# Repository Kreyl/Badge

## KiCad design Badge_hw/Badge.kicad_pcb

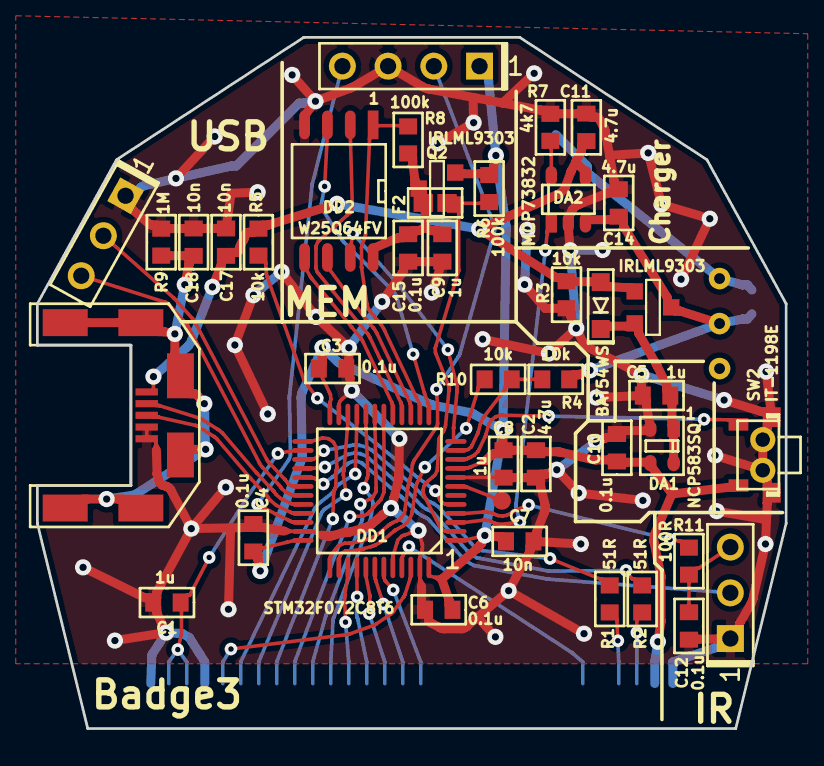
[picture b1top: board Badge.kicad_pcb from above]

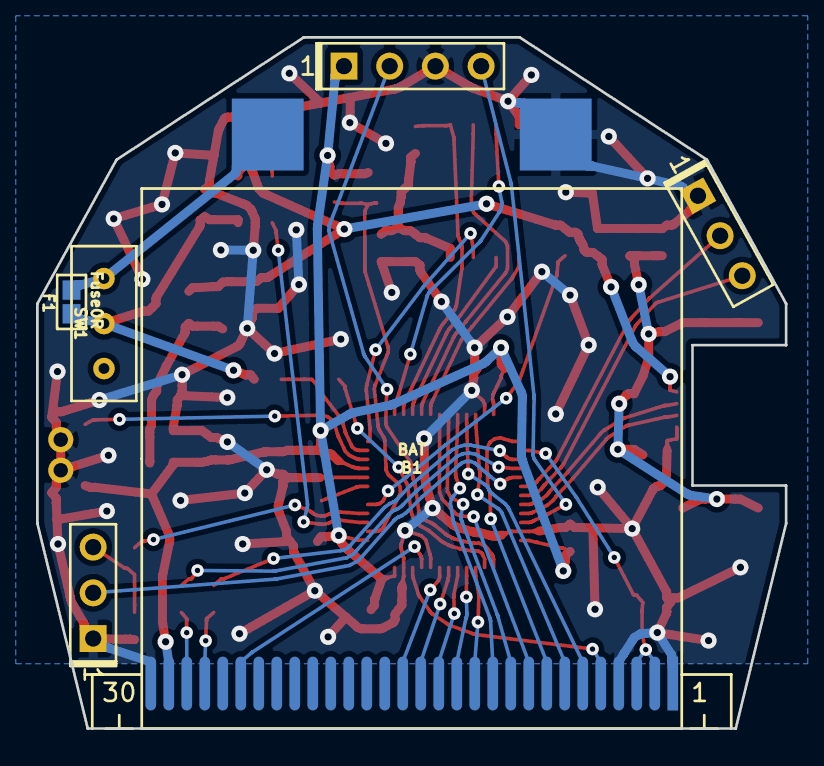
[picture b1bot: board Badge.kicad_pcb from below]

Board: 2 copper layers, 41.6 x 38.4 mm, 45 parts (5 on the bottom side), 49 nets.

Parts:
B1: BAT; EEMB603030
C1, C5, C8, C9: 1u; CAP_0603
C2, C11, C14: 4.7u; CAP_0603
C3, C4, C6, C10, C12, C15: 0.1u; CAP_0603
C7, C17, C18: 10n; CAP_0603
D1: BAT54WS; SOD323
DA1: NCP583SQ; SC82AB
DA2: MCP73832; SOT23-5
DD1: STM32F072C8T6; LQFP48
DD2: W25Q64FV; SO8_208MIL
F1, F2: Fuse0R; RES_0603_FUSE
Q1, Q2: IRLML9303; SOT23-3
R1, R2: 51R; RES_0603
R3, R4, R5, R10: 10k; RES_0603
R6, R8: 100k; RES_0603
R7: 4k7; RES_0603
R9: 1M; RES_0603
R11: 100R; RES_0603
SW1: SWITCH; SW_SS-1P2T
SW2: IT-1198E; BTN_IT1198
TP1: TESTPOINT; TESTPOINT_1MM
U1: Round2.2; Round2_2
XL1: ST_SWD; PLS-4
XL2: USB_MINI_B; USBmicro_MOLEX_WM17142
XL3, XL4: CONN_3; PLS-3

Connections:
+3.3V: C2.1, C3.1, C4.1, C6.1, C7.1, C8.1, C10.1, DA1.3, DD1.1, DD1.9, DD1.24, DD1.36, DD1.48, Q2.2, R6.1, SW2.1, U1.29, XL1.1
+5V: C11.1, C17.2, D1.A, DA2.4, Q1.1, R3.1, R5.1, XL2.1
+BATT: C14.1, DA2.3, F1.1, Q1.3, R4.1, SW1.2
/BAT: B1.A, F1.2, SW1.1
/BatMeas: DD1.11, R4.2, R10.1
/Btn: DD1.10, SW2.2
/Charge: DA2.1, DD1.3
/D00: DD1.18, U1.9
/D01: DD1.19, U1.10
/D02: DD1.20, U1.11
/D03: DD1.39, U1.12
/D04: DD1.40, U1.13
/D05: DD1.41, U1.14
/D06: DD1.42, U1.15
/D07: DD1.43, U1.16
/D+: DD1.33, XL2.3
/D-: DD1.32, XL2.2
/IR_PWR: DD1.4, R11.2
/IR_RX: DD1.29, XL4.2
/LCD_CS: DD1.46, U1.5
/LCD_PWR: C1.1, DD1.26, U1.2, U1.3
/LCD_RD: DD1.25, U1.8
/LCD_RS: DD1.21, U1.6
/LCD_RST: DD1.45, U1.25
/LCD_WR: DD1.22, U1.7
/LED_C1: DD1.27, R1.1
/LED_C2: DD1.28, R2.1
/MEM_CLK: DD1.15, DD2.6
/MEM_CS: DD1.14, DD2.1, R8.2
/MEM_DI: DD1.17, DD2.5
/MEM_DO: DD1.16, DD2.2
/MEM_HOLD: DD1.12, DD2.7
/MEM_PWR: C9.1, C15.1, DD2.8, F2.2, Q2.3, R8.1
/MEM_PWR_CTRL: DD1.2, F2.1, Q2.1, R6.2
/MEM_WP: DD1.13, DD2.3
/RX: DD1.31, XL3.3
/SHLD: C18.1, R9.1, XL2.SHLD
/SWCLK: DD1.37, XL1.2
/SWDIO: DD1.34, XL1.4
/TX: DD1.30, XL3.2
/V_OUT: C5.1, D1.C, DA1.1, DA1.4, Q1.2
GND: B1.C, C1.2, C2.2, C3.2, C4.2, C5.2, C6.2, C7.2, C8.2, C9.2, C10.2, C11.2, C12.1, C14.2, C15.2, C17.1, C18.2, DA1.2, DA2.2, DD1.8, DD1.23, DD1.35, DD1.44, DD1.47, DD2.4, R3.2, R7.2, R9.2, SW2.H, U1.1, U1.4, U1.30, XL1.3, XL2.4, XL2.5, XL3.1, XL4.1
unnamed: C12.2, R11.1, XL4.3
unnamed: DA2.5, R7.1
unnamed: DD1.5, R5.2
unnamed: DD1.7, TP1.1
unnamed: DD1.38, R10.2
unnamed: R1.2, U1.27
unnamed: R2.2, U1.28

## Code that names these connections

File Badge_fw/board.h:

/*
 * board.h
 *
 *  Created on: 12 ñåíò. 2015 ã.
 *      Author: Kreyl
 */

#pragma once

#include <inttypes.h>

// ==== General ====
#define BOARD_NAME          "Badge3"
// MCU type as defined in the ST header.
#define STM32F072xB

// Freq of external crystal if any. Leave it here even if not used.
#define CRYSTAL_FREQ_HZ     12000000

#define SYS_TIM_CLK         (Clk.APBFreqHz * Clk.TimerClkMulti)

#if 1 // ========================== GPIO =======================================
// UART
#define UART_GPIO       GPIOA
#define UART_TX_PIN     9
#define UART_RX_PIN     10
#define UART_AF         AF1

// USB
#define USB_GPIO		GPIOA
#define USB_DM_PIN		11
#define USB_DP_PIN		12
#define SNS_5V_GPIO     GPIOF
#define SNS_5V_PIN      0

// Button
#define BTN_GPIO        GPIOA
#define BTN_PIN         0

// Battery Management
#define BAT_MEAS_GPIO   GPIOA
#define BAT_MEAS_PIN    1
#define BAT_SW_GPIO     GPIOA
#define BAT_SW_PIN      15
#define BAT_CHARGE_GPIO GPIOC
#define BAT_CHARGE_PIN  14

#if 1 // ==== LCD ====
#define LCD_GPIO        GPIOB
#define LCD_RST         8
#define LCD_CS          9
#define LCD_RS          10
#define LCD_WR          11
#define LCD_RD          12
#define LCD_PWR         13
#define LCD_MODE_MSK_READ   0xFFFF0000
#define LCD_MODE_MSK_WRITE  0x00005555
#define LCD_BCKLT_GPIO  GPIOB
#define LCD_BCKLT_PIN1  14
#define LCD_BCKLT_PIN2  15
#endif // LCD

#if 1 // ==== Flash W25Q64 ====
#define MEM_GPIO        GPIOA
#define MEM_CS          4
#define MEM_CLK         5
#define MEM_DI          7
#define MEM_DO          6
#define MEM_WP          3
#define MEM_HOLD        2
#define MEM_PWR_GPIO    GPIOC
#define MEM_PWR         13
#define MEM_SPI_AF      AF0
#endif // Flash

#endif // GPIO

#if 1 // ========================= Timer =======================================
// LCD
#define LCD_BCKLT_TMR   TIM15
#define LCD_BCKLT_CHNL1 1
#define LCD_BCKLT_CHNL2 2
#endif // Timer

#if 1 // =========================== SPI =======================================
#define MEM_SPI         SPI1
#endif

#if 1 // ========================== USART ======================================
#define UART            USART1
#define UART_TX_REG     UART->TDR
#define UART_RX_REG     UART->RDR
#endif

#if 1 // ========================= Inner ADC ===================================
#define ADC_REQUIRED        TRUE
// Clock divider: clock is generated from the APB2
#define ADC_CLK_DIVIDER		adcDiv2

// ADC channels
#define BAT_CHNL 	        1

#define ADC_VREFINT_CHNL    17  // All 4xx and F072 devices. Do not change.
#define ADC_CHANNELS        { BAT_CHNL, ADC_VREFINT_CHNL }
#define ADC_CHANNEL_CNT     2   // Do not use countof(AdcChannels) as preprocessor does not know what is countof => cannot check
#define ADC_SAMPLE_TIME     ast55d5Cycles
#define ADC_SAMPLE_CNT      8   // How many times to measure every channel

#define ADC_MAX_SEQ_LEN     16  // 1...16; Const, see ref man
#define ADC_SEQ_LEN         (ADC_SAMPLE_CNT * ADC_CHANNEL_CNT)
#if (ADC_SEQ_LEN > ADC_MAX_SEQ_LEN) || (ADC_SEQ_LEN == 0)
#error "Wrong ADC channel count and sample count"
#endif
#endif

#if 1 // ========================== USB ========================================
#define USBDrv          USBD1   // USB driver to use

// CRS
#define CRS_PRESCALER   RCC_CRS_SYNC_DIV1
#define CRS_SOURCE      RCC_CRS_SYNC_SOURCE_USB
#define CRS_POLARITY    RCC_CRS_SYNC_POLARITY_RISING
#define CRS_RELOAD_VAL  ((48000000 / 1000) - 1) // Ftarget / Fsync - 1
#define CRS_ERROR_LIMIT 34
#define HSI48_CALIBRATN 32
#endif // USB

#if 1 // =========================== DMA =======================================
#define STM32_DMA_REQUIRED  TRUE
// ==== Uart ====
// Remap is made automatically if required
#define UART_DMA_TX     STM32_DMA1_STREAM4
#define UART_DMA_RX     STM32_DMA1_STREAM5
#define UART_DMA_CHNL   0   // Dummy

// ==== Memory ====
#define SPI1_DMA_RX     STM32_DMA1_STREAM2

#define MEMCPY_DMA      STM32_DMA1_STREAM3
#define MEM_CPY_DMA_MODE STM32_DMA_CR_CHSEL(0) |    /* dummy */ \
                        STM32_DMA_CR_PL(0b10) |     /* DMA_PRIORITY_HIGH */ \
                        STM32_DMA_CR_MSIZE_BYTE | \
                        STM32_DMA_CR_PSIZE_BYTE

#if ADC_REQUIRED
/* DMA request mapped on this DMA channel only if the corresponding remapping bit is cleared in the SYSCFG_CFGR1
 * register. For more details, please refer to Section10.1.1: SYSCFG configuration register 1 (SYSCFG_CFGR1) on
 * page173 */
#define ADC_DMA         STM32_DMA1_STREAM1
#define ADC_DMA_MODE    STM32_DMA_CR_CHSEL(0) |   /* DMA2 Stream4 Channel0 */ \
                        DMA_PRIORITY_LOW | \
                        STM32_DMA_CR_MSIZE_HWORD | \
                        STM32_DMA_CR_PSIZE_HWORD | \
                        STM32_DMA_CR_MINC |       /* Memory pointer increase */ \
                        STM32_DMA_CR_DIR_P2M |    /* Direction is peripheral to memory */ \
                        STM32_DMA_CR_TCIE         /* Enable Transmission Complete IRQ */
#endif // ADC

#endif // DMA

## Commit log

2015-12-15 First version. Archive purposes.
2015-12-23 + Badge2 sch completed
2015-12-24 + Sch completed + Board design started
2016-01-26 Badge2 pcb routed
2016-01-26 + OS and UART with DMA
2016-01-26 + LCD backlight
2016-01-27 + Reg read/write
2016-01-27 + CLS works
2016-01-27 + Rectangle filling successful
2016-01-28 + PutBitmap + Offset added
2016-01-28 + Flash memory class + Flash ID check
2016-01-29 * SPI 8bit fixed + BusyWait + Write
2016-01-29 Read, write, erase
2016-01-29 + Proceeding with USB
2016-01-30 + host sees it as MSD and tries to communicate + Debug added to Chibios
2016-01-30 + msd works
2016-01-30 + FatFs, not working
2016-01-30 * MSD block sz = 512 * FatFS works
2016-01-30 * 4096 bytes block sz, works ok
2016-01-30 + Memory Read/Write functions semaphored
2016-01-30 Button works, file opens
2016-01-30 + bmp drawn
2016-01-30 + Bmp with reversed row order implemented
2016-01-31 No Long Filename
2016-01-31 - LongFileNames (no need in them here) * Continuous picture redraw fixed
2016-01-31 + MCU freq increased to speed-up picture displaying. HSI48 does not switches off, though.
2016-02-01 * DisableHSI48() fixed (did not switch off) + HiFreq on before and off after pic draw
2016-02-01 + Evtmsk LcdDone - Usb.IsReady * Backlight off when redraw
2016-02-01 + USB off and on ok + HSI48 on and off ok
2016-02-02 + Memory read through DMA
2016-02-02 Fast read, no write
2016-02-02 - MEM TX DMA Back to no-DMA write. Works ok.
2016-02-02 + SCSI commands: 1B and 35
2016-02-03 + LCD & Memory shutdown methods
2016-02-03 + button longpress
2016-02-03 + ADC battery measurement + Battery display in progress
2016-02-03 Proceeding
2016-02-03 + DrawBattery ok
2016-02-03 + Pics nearly done * Switch to HSI moved to Clk + Draw NoFile image
2016-02-03 * In case of battery redraw, only battery redrawn
2016-02-03 * SimpleSensors thd priority made higher * Semaphores removed, replaced with chSysLock
2016-02-03 + Shutdown implemented, but works bad * Charging current set resistor 4k7
2016-02-04 - Button longpress - Button shutdown
2016-02-04 * WhatNext
2016-02-05 * USB communication with MacOs fixed * Battery constants changed to 4140-3340mV
2016-02-05 + Mem WriteProtection when not writing + Mem Reset before trying FS mounting
2016-02-05 * LCD WriteBuf moved to RAM
2016-02-06 * __RAMFUNC modified * Battery draw cleaned
2016-02-06 + Delay after mem reset
2016-02-06 Proceeding with gif
2016-02-14 Last try to display GIF, completed by half
2016-02-16 Proceeding with sch
2016-02-16 + Badge3 PCB completed
2016-02-28 - Clocking + RLE decompressor
2016-02-28 * Speed improved by replacing memcpy with DMA
2016-02-28 + bmp 24bit
2016-02-29 + bmp 1bit
2016-02-29 + bmp 8
2016-02-29 + bmp 4
2016-02-29 * bmp 16bit improved + bmp32 (not tested)
2016-02-29 Small pic centered
2016-03-03 + Pics Proceeding
2016-03-04 + Config parser
2016-03-04 draw broken
2016-03-04 + Read/Write operations successfully defended by semaphore + Images switch without fade
2016-03-04 + FadeIn and FadeOut
2016-03-06 * new led version
2016-03-07 Iterating images within several dirs
2016-03-07 + Img auto works
2016-03-07 Img switch ok
2016-03-07 * Prefetch enabled
2016-03-07 + Shutdown + FS remount when start img search over to catch new files
2016-03-08 B3 ok, B2 mem fail
2016-03-08 Seems works both
2016-03-08 * Long file names allowed, seems working
2016-03-08 Long filenames in progress
2016-03-08 + Backlight On/Off during redraw. Works, but is bad idea.
2016-03-08 - Backlight on/off option removed RC
2016-03-09 * Fixed uint32_t time Release
2016-07-07 Release
